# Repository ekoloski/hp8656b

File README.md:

## HP1820-3618 replacement

This project aims to use modern hardware to recreate the functionality of a mask rom microcontroller known as 1820-3618 in HP catalogs. It was used in the HP 8656B Signal Generator, and possibly other equipment, to interface the generators main cpu with both the fractional-n divider asic and various modulation circuits. It's a serial to parallel converter that also manages some gpio control lines.

The service manual describes a high level overview of the chips functions but lacks enough detail to create a suitable replacement. As I later found out, this firmware also does a couple of interesting things in response to a few serial commands I've never seen my 8656B issue. It also provides some routines for troubleshooting the rest of the circuitry.

### But...why go to the effort when you can just get one from a junk unit?

I purchased this signal generator on one of the auction sites with the understanding that it was for parts only and needed repair. My goal from the start was to restore the unit and use it as part of my electronics lab. After quite a bit of debugging I ultimately traced the issues to a failing adjustment potentiometer and a failed transistor. This is where the story should happily end, however it does not. In the course of troubleshooting I did some sloppy probing around A13U9 which led to the introduction of **-15V** to the 'Out of Lock' comparator output pin, which is directly connected to pin 11 of the 1820-3618, A13U28.

The chip never functioned properly after that event. The unit was not able to achieve PLL lock even after the original faults were discovered and repaired. I probed the serial input of A13U28 and found data. I then probed the 4 parallel output pins and the control lines, still no activity.

I was unable to find any information on this chip, labeled as a Motorola SC87336CP. Comparing the pinout in the 8656B service manual I found it to be fairly unique pinout in the world of Motorola 8bit microcontrollers of the time. Some educated guesses led me to the MC68705P5, which fit the description. I suspect that my chip is a mask rom variant of this microprocessor. Which is great, but without the ability to read the ROM I am still stuck.

Thinking that it was a lost cause to recreate the chip at this point I decided to purchase a second 8656B in much worse cosmetic condition. The part was harvested, transplanted, and the repaired unit works great. Everything should have been wonderful! Unfortunately I decided to investigate what in addition to a missing A13U28 was wrong with the donor unit. Much to my disappointment, the only problem was a faulty electrolytic capacitor. Of course I had to replace it but now I'm back to the start and stuck with an otherwise functional boat anchor in need of one unobtanium chip.

### Extracting the ROM

After quite a bit of reading I had come to the belief that the chip would need to be carefully decapped and photographed under a microscope. It could then be possible to locate the ROM on the die and optically recover the bits. I've seen it done on the internet, so it's got to be easy, right?

Probably not. So I shelved this project in lieu of some others and spent a while just not thinking about it. Then I did a little more research and came across the work by [Sean Riddle](http://seanriddle.com/mc68705p5.html). He details an obscure operating mode of the same family of CPU, and how he exploited it.

This mode is entered by powering the chip with /RESET /INT and TIMER high, and pulling PC0 high to 7.5V. When the micro comes out of reset it will ingest opcodes to execute from PortA. At the same time, an output is latched onto PortB. If the instruction on PortA happens to be 0x9d (nop) then the chip will simply continue to iterate through all 2K of it's address space. The output on PortB is a permutation of the current address, and the contents in memory. There is also apparently some data on PortC, but that's damaged on my chip so I didn't bother. I suspect it's the missing bits of the address.

As mentioned, the damage to my chip was conveniently located on PortC. Maybe there's hope that this method works on my particular mask rom, and that it's not too badly damaged? I figured it's worth a shot, so I breadboarded everything up and hooked up the scope.

To my amazement, there was data. A stream of it! The byte is sampled on the falling edge of each clock, 8 clocks are required to produce one byte of actual data, as it appears in the form of:
    {ADDR} {ADDR} {DATA} {DATA} {ADDR} {ADDR} {DATA} {DATA}

I noticed that the pattern was repeating at each 16K boundary, meaning we have a 2K address space. The chip will happily loop through and read out the address space until reset.

A healthy chunk of data was captured on the logic analyzer. The data was sifted from the noise to produce a raw dump.

### Interpreting the ROM

Next I needed to figure out what I was looking at. Nothing lined up with the memory mapping from the MC68705P5's datasheet. I realized that not only did the chip fetch an opcode from PortA, it fetched an address. The 0x9D must have been read in as $59D, meaning my capture started at 1437 bytes in! I shifted the data to realign it and it lined up perfectly with the memory map in the datasheet. I overwrote all non-ROM addresses with 0x9D to make disassembly easier and was ready to disassemble.

The [MAME project](https://www.mamedev.org/) has done a lot of work with this type of micro, and it's no surprise they have a nice disassembler called unidasm, which happily ingested the ROM from my crippled chip.

It took a moment and help from the Motorola M68HC05 Applications Guide, but I was able to wrap my head around the result. The only code I've written for microprocessors has been interrupt driven and was written in C. This is neither of those things. Instead it's beautify simple and elegant.

Beyond that, recreating the functionality of the chip be considerably more difficult without it. There are nuances that are not discussed in the service manual. I've also found that a test pin labeled as unused in the service manual does have a routine associated with it. Perhaps this chip was used in other equipment?

### Converting to something more modern

Now that I have the program from the chip and it's datasheet there's no reason not to create a modern replacement.

I decided on an Atmel ATMEGA32U4-MUR. It was available, came in a small enough package that I could build a board to fit the original DIP-28W, and had more than enough capability for the job. After creating a small breakout board and soldering pin headers to emulate the original DIP28W, I was ready to start adapting the program.

With how purpose built the code is, and with the role it plays in setting up things like the FM calibration and other support circuitry in the 8656B, I suspect that the timings involved may be somewhat critical. I likely wouldn't achieve anything as close to the original if I wrote it in C, unless I did a bunch of extra work. So, AVR8 it is.

### Again...why?

The chances of anyone else needing a replacement for an HP1820-3618 are pretty slim. The chances of finding this and needing a replacement? Negligible.

But I would bet that there are others who may find themselves, for whatever reason, wanting to get a peek into a similar mask rom. I'd be glad if it helps in that case and maybe even resurrects some piece of hardware. It's been a lot of fun, and I've rediscovered a bit of code that, in all likelihood, no one else has even looked at in at least the last 25 years.

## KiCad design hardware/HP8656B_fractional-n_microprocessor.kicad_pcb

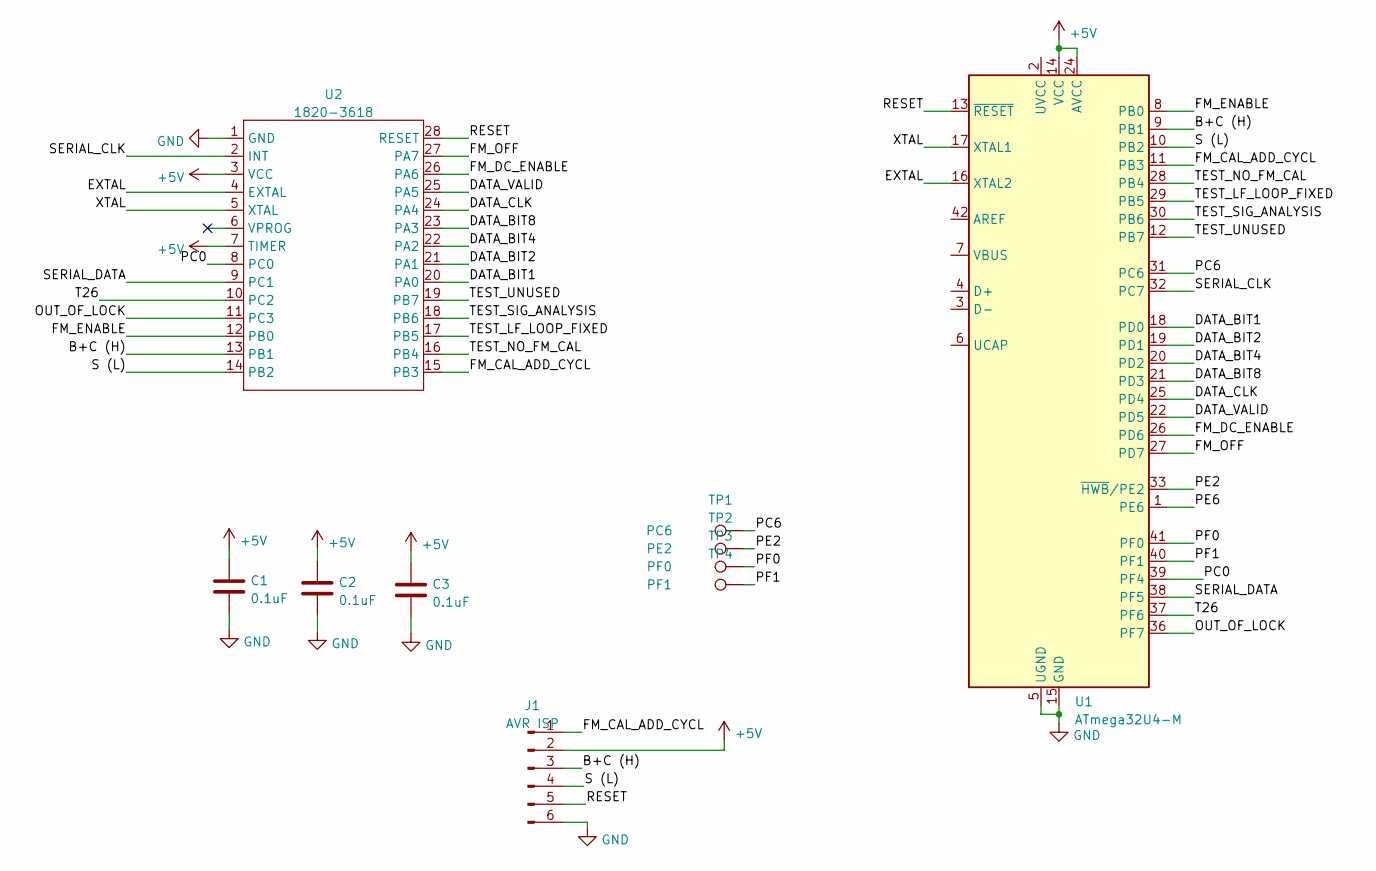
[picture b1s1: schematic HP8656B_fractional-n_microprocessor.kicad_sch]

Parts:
C1, C2, C3: 0.1uF; C_0603_1608Metric
J1: AVR ISP; PinHeader_2x03_P2.54mm_Vertical
TP1: PC6; TestPoint_Pad_D1.0mm
TP2: PE2; TestPoint_Pad_D1.0mm
TP3: PF0; TestPoint_Pad_D1.0mm
TP4: PF1; TestPoint_Pad_D1.0mm
U1: ATmega32U4-M; QFN-44-1EP_7x7mm_P0.5mm_EP5.2x5.2mm
U2: 1820-3618; DIP-28_W15.24mm_Socket

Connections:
+5V: C1.1, C2.1, C3.1, J1.2, U1.14 (VCC), U1.24 (AVCC), U1.34 (VCC), U1.44 (AVCC), U2.3 (VCC), U2.7 (TIMER)
/B+C (H): J1.3, U1.9 (PB1), U2.13 (PB1)
/DATA_BIT1: U1.18 (PD0), U2.20 (PA0)
/DATA_BIT2: U1.19 (PD1), U2.21 (PA1)
/DATA_BIT4: U1.20 (PD2), U2.22 (PA2)
/DATA_BIT8: U1.21 (PD3), U2.23 (PA3)
/DATA_CLK: U1.25 (PD4), U2.24 (PA4)
/DATA_VALID: U1.22 (PD5), U2.25 (PA5)
/EXTAL: U1.16 (XTAL2), U2.4 (EXTAL)
/FM_CAL_ADD_CYCL: J1.1, U1.11 (PB3), U2.15 (PB3)
/FM_DC_ENABLE: U1.26 (PD6), U2.26 (PA6)
/FM_ENABLE: U1.8 (PB0), U2.12 (PB0)
/FM_OFF: U1.27 (PD7), U2.27 (PA7)
/OUT_OF_LOCK: U1.36 (PF7), U2.11 (PC3)
/PC0: U1.39 (PF4), U2.8 (PC0)
/PC6: TP1.1, U1.31 (PC6)
/PE2: TP2.1, U1.33 (~HWB/PE2)
/PE6: U1.1 (PE6)
/PF0: TP3.1, U1.41 (PF0)
/PF1: TP4.1, U1.40 (PF1)
/RESET: J1.5, U1.13 (~RESET), U2.28 (RESET)
/S (L): J1.4, U1.10 (PB2), U2.14 (PB2)
/SERIAL_CLK: U1.32 (PC7), U2.2 (INT)
/SERIAL_DATA: U1.38 (PF5), U2.9 (PC1)
/T26: U1.37 (PF6), U2.10 (PC2)
/TEST_LF_LOOP_FIXED: U1.29 (PB5), U2.17 (PB5)
/TEST_NO_FM_CAL: U1.28 (PB4), U2.16 (PB4)
/TEST_SIG_ANALYSIS: U1.30 (PB6), U2.18 (PB6)
/TEST_UNUSED: U1.12 (PB7), U2.19 (PB7)
/XTAL: U1.17 (XTAL1), U2.5 (XTAL)
GND: C1.2, C2.2, C3.2, J1.6, U1.5 (UGND), U1.15 (GND), U1.23 (GND), U1.35 (GND), U1.43 (GND), U1.45 (GND), U2.1 (GND)

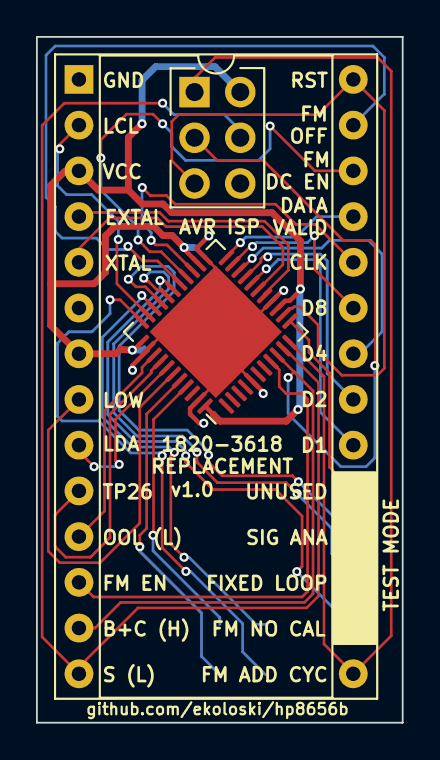
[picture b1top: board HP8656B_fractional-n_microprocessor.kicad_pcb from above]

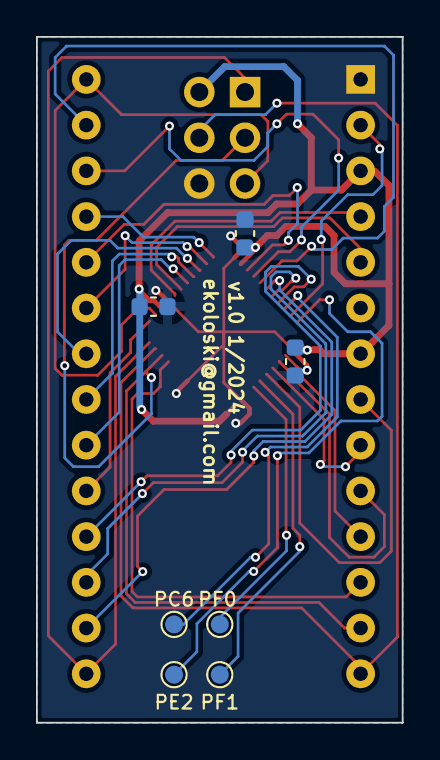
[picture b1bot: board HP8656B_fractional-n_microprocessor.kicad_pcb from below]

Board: 2 copper layers, 20.3 x 38.1 mm, 10 parts (7 on the bottom side), 30 nets.

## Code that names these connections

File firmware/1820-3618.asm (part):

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    out     SPH,r16             ;

    ldi     r16,0xFF            ;
    out     DDRD,r16            ; set PORTD PD0:7 Output
    ldi     r16,0x05            ;
    out     PORTB,r16           ; set PB0 `fm_en` and PB2`S_L` high
    ldi     r16,0x0F            ;
    out     DDRB,r16            ; set PB0:PB3 Output
    ldi     r16,0xF0            ; 
    out     PORTB,r16           ; Set pull-ups on test mode input pins PB4:7
    sbi     PORTC,7             ; set PC7 pull-up
    sbi     PORTC,6             ; set PC6 pull-up `TP26`

    sbis    PINF,6
    rjmp    test_mode_tp26      ; if PF6 `TP26` is low then jump to TP26 routine
    rjmp    main                ; otherwise proceed to main program

test_mode_tp26:
    sbis    PINB,5                          ; if PB5 `Test mode fixed loop` is LOW
    jmp     testmode_lf_loop_vco_fixed      ;  jump to fixed loop routine
    sbis    PINB,6                          ; if PB6 `Signal Analysis` mode is LOW 
    jmp     testmode_signature_analysis     ;  jump to sig ana routine
    sbis    PINB,7
    jmp     testmode_unused                 ; if PB7 `Unused` is LOW jump to unused test routine
                                            ; Service manual lists as unused, but it jumps into
                                            ; signal analysis at an alternate point.
    rjmp    test_mode_tp26                  ; We're stuck here until a test mode is selected
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    ld      r16,X               ; Load the first word from the buffer and wait to receive
receive_command:
    sbic    PINC,7
    rjmp    receive_command     ; wait for PC7 `SCL` to go low
    sbis    PINF,5              ; 
    clc                         ; funny little dance
    sbic    PINF,5              ; to get the data bit into the carry bit
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                                ;  It's cooler in m6805 due to the indexed address mode on rol    
command_clockwait:
    sbis    PINC,7
    rjmp    command_clockwait   ; wait for PC7 `SCL` to go high
    brcc    receive_command     ; Loop to receive the word
    st      X,r16
    sbrs    r16,3               ; check if command is 0-7 and go run it
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    ld      r16,x
receive_bits:
    sbic    PINC,7
    rjmp    receive_bits        ; wait for PC7 `SCL` to go low
    sbis    PINF,5
    clc                         ; Transfer to carry
    sbic    PINF,5
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command_1:                      ; Report the status of OOL on the Serial Data line
    cbi     PORTF,5             ; This is used in the built-in self tests under option `6`
    sbic    PINF,7              ;
    sbi     PORTF,5             ; Transfer status of PF7 `OOL` to PF5 `SDA`
    ldi     r16,0x20            ;
    out     DDRF,r16            ; set PF5 `serial data in` as output
    ldi     r16,0x0D            ; Delay a moment
command_1_delay:
    dec     r16
    brne    command_1_delay
    ldi     r16,0x00
    out     DDRF,r16            ; Set PF5 `serial data in` back to an input
    sbi     PORTF,5             ; Set the pullup on PF5
    jmp     main                ; Back to program start

command_2:                      ; FM Disable
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    ret

                                ; 4-bit parallel data out. Data is valid on rising edge of clk
                                ; This also preserves the status of control lines PD6:7
tx_parallel_data:               ; Wake up the Fractional-N controller
    ldi     r16,0x01            ; Set r16 to 0x01
    ld      r17,Y               ; Load the status byte into r17
    or      r16,r17
    out     PORTD,r16           ; Set PD0 `D1` high
    ori     r16,0x20
    out     PORTD,r16           ; Set PD5 `data_valid`
    nop                         ; Pulse stretcher
    andi    r16,0xCF            ; Clear data_valid and clk bits
    out     PORTD,r16
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    ldi     XH,HIGH(sStatus)
    ld      r16,X
    ori     r16,0x40
    out     PORTD,r16           ; Set PD6 `fm_dc_en` set the remaining bits from sStatus
    ldi     r16,0x0B
    out     PORTB,r16           ; Set `fm_en`, `B+C` and `fm_add_cyc`
    call    delay_60mS          ; wait 60 milliseconds
    sbi     PORTB,2             ; Set PB2 `S (L)` pin
    cbi     PORTB,3             ; Clear PB3 `fm_add_cyc` pin
fm_cal_delay:
    ldi     r16,0x08            ; 
    out     OCR0A,r16           ; Set compareA to 0x08, about 5mS
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    inc     r16
    cpi     r16,0x2e            ;
    brne    fm_cal_delay_2
    cbi     PORTB,1             ; Clear PB1 `B+C H`
    eor     r16,r16             ; Clock/Prescaler comination don't have enough resolution
fm_cal_delay_3:                 ; Extra delay before setting port back to stored status
    inc     r16
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    ld      r16,X               ; Load sStatus into r16
    sbrc    r16,7               ; Keep 'fm_en' pin set if status was already enabled
    rjmp    fm_cal_done
    cbi     PORTB,0             ; Otherwise clear PB0 `fm_en` pin
fm_cal_done:
    ldi     XL,LOW(sStatus)
    ldi     XH,HIGH(sStatus)
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                                        ; low, the signature at the related pin is the alternate
                                        ; signature

                                        ;PB0 TP24 CLK fm_enable
                                        ;PB1 TP25 DSA B+C L (start_stop)
                                        ;OOL is LOW when LED is lit

                                        ;PIN            NORMAL      ALTERNATE   Condition
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                                        ;6(VPP)         0000        ----        ----
                                        ;7(HIGH)        7U39        ----        ----
                                        ;8(LOW)         0000        ----        ----
                                        ;9(SDA)         0000        7U39        PF5 pulled high
                                        ;10(TP26)       7U39        0000        PF6 tied low
                                        ;11(OOL)        7U39        0000        Out of Lock LED on
                                        ;14(S (L))      0021        0020        INT pin low
                                        ;15(fm_add_cyc  0010        40C5        RAM Error
                                        ;16(S (L))      7U39        0000        PB4 tied low
                                        ;17(fixed_loop) 7U39        0000        PB5 tied low
                                        ;18(sig_ana)    7U39        0000        PB6 tied low
                                        ;19(unused)     7U39        0000        PB7 tied low
                                        ;20(D1)         2050        2052        PF4 low
                                        ;21(D2)         102C        1029        PF5 low
                                        ;22(D4)         0816        0814        PF6 low
                                        ;23(D8)         0408        040A        Out of Lock LED ON
                                        ;24(PCLK)       0201        0205        PB4 low
                                        ;25(data_valid) 0105        0102        PB5 low
                                        ;26(fm_dc_en)   0085        0081        PB6 low
                                        ;27(fm_off)     0044        0040        PB7 low
                                        ;28 RESET       7U39        ----        ----
testmode_signature_analysis:
    ldi     r16,0x00
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    brcc    ramtest_resetX      ; branch if carry is clear to start over
    rjmp    rampass
ramfail:
    sbi     PORTB,3             ; Set PB3 `fm_add_cyc`
rampass:
    eor     r17,r17             ; Clock/Prescaler combination doesn't have enough resolution.
ramtest_padding:                ; Timing here is not critical, regardless a delay is added
    inc     r17                 ; to more closely match the original.
    cpi     r17,0x02
    brne    ramtest_padding
    sbi     PORTB,1             ; Set bit PB1 `B+C H` (Open SA window)
    call    dsa_clock           ; Clock the signature analyzer
    cbi     PORTB,3             ; Clear bit PB3 `fm_add_cyc`
    ldi     r16,0x01
bit_shift_loop:                 ; Walk a bit through PORTD
    out     PORTD,r16           ; Update PORTD
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    brcc    bit_shift_loop      ; Walk through the entire port
    clr     r16
    out     PORTD,r16           ; Clear PORTD
    sbi     PORTB,2             ; Set PB2 `S (L)`
    call    dsa_clock           ;
    cbi     PORTB,2             ; Clear PB2 `S (L)`
    sbi     PORTB,3             ; Set PB3 `FM_CAL_ADD_CYC`
    call    dsa_clock           ;
    cbi     PORTB,3             ; Clear PB3 `FM_CAL_ADD_CYC`
    clr     r16
    out     PORTD,r16           ; Clear PORTD
    call    dsa_clock           ; Clock the signature analyzer
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    out     PORTD,r16           ; Clear PORTD
    jmp     testmode_unused

dsa_clock:                      ; Deliver a brief pulse to `fm_en` pin PB0
    sbi     PORTB,0
    nop
    nop
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    ret

testmode_unused:
    sbis    PINC,7              ; If PC7 `serial_clock_in` is low then clear PB2 and clock sig ana
    rjmp    test_mode_1
    sbi     PORTB,2             ; Otherwise set PB2 `S (L)`
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
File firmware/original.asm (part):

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00000080: a6 ff     lda   #$FF          ;
00000082: b7 04     sta   $04           ;set PORTA output
00000084: a6 80     lda   #$80          ;
00000086: b7 00     sta   $00           ;set PA7 (fm_off) high
00000088: b7 40     sta   $40           ;
0000008a: a6 0f     lda   #$0F          ;
0000008c: b7 05     sta   $05           ;set PB0:PB3 output
0000008e: a6 05     lda   #$05          ;
00000090: b7 01     sta   $01           ;set PB0 and PB2 `fm_en` and `S (L)` high
00000092: a6 00     lda   #$00
00000094: b7 06     sta   $06           ;set PORTC input

                                        ; Check test mode `TP26` is low
00000096: 05 02 03  brclr 2, $02, $09C  ;if PC2 `TP26` is low branch and check which mode to run
00000099: cc 03 c0  jmp   $03C0         ;else jump to the main program

0000009c: 0a 01 03  brset 5, $01, $0A2  ;if PB5 `TEST MODE FIXED LOOP` is low
0000009f: cc 05 b3  jmp   $05B3         ;jump to $5B3 [Test Mode Fixed Loop]

000000a2: 0c 01 03  brset 6, $01, $0A8  ;if PB6 (TEST MODE SIG ANA) is low
000000a5: cc 05 f0  jmp   $05F0         ;jump to $5F0 [Test Mode SIG ANA]

000000a8: 0e 01 f1  brset 7, $01, $09C  ;if PB7 (TEST MODE UNUSED) is low
000000ab: cc 06 64  jmp   $0664         ;jump to $664 [Test Mode UNUSED]
          ; Service manual lists this as unused but it jumps into an alternate point of sig analysis

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00000420: a4 02     anda  #$02          ;
00000422: b7 02     sta   $02           ;
00000424: a6 02     lda   #$02          ;
00000426: b7 06     sta   $06           ;Set PC1 as an output (Serial Data Pin)
00000428: ae 0d     ldx   #$0D          ;
0000042a: 5a        decx                ;
0000042b: 26 fd     bne   $42A          ; delay loop (52 cycles about 13 uS)
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                                        ; [Send all 16 words and associated control signals]
0000046b: a6 01     lda   #$01          ; load 0x01 into A
0000046d: ba 40     ora   $40           ; or sStatus with A
0000046f: b7 00     sta   $00           ;store A into PortA setting PA0 `D1` and PA6 `fm_dc_en`
00000471: aa 20     ora   #$20          ;or A with 0x20 (0x61)
00000473: b7 00     sta   $00           ;bring PA5 `data_valid` high as well
00000475: a4 cf     anda  #$CF          ;
00000477: b7 00     sta   $00           ;clear PA5 `data_valid`
00000479: ae 06     ldx   #$06          ;
0000047b: 5a        decx                ;
0000047c: 26 fd     bne   $47B          ; delay
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00000564: a6 0b     lda   #$0B          ;
00000566: b7 01     sta   $01           ;set `fm_en`, `B+C`, and `fm_add_cyc`
00000568: cd 05 98  jsr   $0598         ;delay
0000056b: 14 01     bset  2, $01        ;set PB2 `S (L)`
0000056d: 17 01     bclr  3, $01        ;clear PB3 `FM Add Cycle`
0000056f: a6 27     lda   #$27          ;
00000571: b7 08     sta   $08           ;
00000573: 3f 09     clr   $09           ;
00000575: 0f 09 fd  brclr 7, $09, $575  ;Calibrated delay
00000578: 13 01     bclr  1, $01        ;clear PB1 `B+C`
0000057a: ae 05     ldx   #$05          ;
0000057c: 5a        decx                ;
0000057d: 26 fd     bne   $57C          ;delay
0000057f: 0e 40 02  brset 7, $40, $584  ;skip if bit 7 of $40 is set
00000582: 11 01     bclr  0, $01        ;clear bit PB0 `FM EN`
00000584: b6 40     lda   $40           ;
00000586: b7 00     sta   $00           ;
00000588: 05 02 01  brclr 2, $02, $58C  ;skip extra delay if `TP26` is low
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                                        ;   A3TP17 to GND
                                        ; The alternate signature at pins 14, 20, 27 check the input at pins 2, 8 to 11 and 16 to 19. When the input is low, the signature at the related pin is the alternate signature

                                        ;PB0 TP24 CLK fm_enable
                                        ;PB1 TP25 DSA B+C L

                                        ;PIN            NORMAL      ALTERNATE   Condition
                                        ;1(VSS)         0000        ----        ---
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                                        ;6(VPP)         0000        ----        ----
                                        ;7(HIGH)        7U39        ----        ----
                                        ;8(LOW)         0000        ----        ----
                                        ;9(SDA)         0000        7U39        PC1 pulled high
                                        ;10(TP26)       7U39        0000        PC2 tied low
                                        ;11(OOL)        7U39        0000        Out of Lock LED on
                                        ;14(S (L))      0021        0020        INT pin low
                                        ;15(fm_add_cyc  0010        40C5        RAM Error
                                        ;16(S (L))      7U39        0000        PB4 tied low
                                        ;17(fixed_loop) 7U39        0000        PB5 tied low
                                        ;18(sig_ana)    7U39        0000        PB6 tied low
                                        ;19(unused)     7U39        0000        PB7 tied low
                                        ;20(D1)         2050        2052        PC0 low
                                        ;21(D2)         102C        1029        PC1 low
                                        ;22(D4)         0816        0814        PC2 low
                                        ;23(D8)         0408        040A        Out of Lock LED ON
                                        ;24(PCLK)       0201        0205        PB4 low
                                        ;25(data_valid) 0105        0102        PB5 low
                                        ;26(fm_dc_en)   0085        0081        PB6 low
                                        ;27(fm_off)     0044        0040        PB7 low
                                        ;28 RESET       7U39        ----        ----
                                        ;
000005f0: 3f 00     clr   $00           ;clear portA
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00000601: ab 11     adda  #$11          ;otherwise add 0x11 to A
00000603: 24 f1     bcc   $5F6          ; jump to back to the start if carry is clear
00000605: 20 02     bra   $609          ;do NOT set fm_add_cyc bit
00000607: 16 01     bset  3, $01        ;set PB3 `fm_add_cyc`
00000609: 12 01     bset  1, $01        ;set PB1 `b+c H`

0000060b: cd 06 5f  jsr   $065F         ;DSA Clock (pulse `fm_en`)
0000060e: 17 01     bclr  3, $01        ;clear PB3 `fm_add_cyc`

00000610: a6 01     lda   #$01          ;
bit_shift_loop:
00000612: b7 00     sta   $00           ;store A into PortA
00000614: cd 06 5f  jsr   $065F         ;DSA Clock (pulse `fm_en`)
00000617: 48        asla                ;left shift A
00000618: 24 f8     bcc   $612          ; jump back to set PA0 if carry is clear
0000061a: 3f 00     clr   $00           ;clear PortA
0000061c: 14 01     bset  2, $01        ;set PORTB bit 2 `S (L)`
0000061e: cd 06 5f  jsr   $065F         ;DSA Clock (pulse `fm_en`)
00000621: 15 01     bclr  2, $01        ;clear PORTB bit 2 `S (L)`
00000623: 16 01     bset  3, $01        ;set PORTB bit 3 `FM_CAL_ADD_CYC`
00000625: cd 06 5f  jsr   $065F         ;DSA Clock (pulse `fm_en`)
00000628: 17 01     bclr  3, $01        ;clear PB3 `fm_add_cyc`

0000062a: 3f 00     clr   $00           ;clear PortA
0000062c: cd 06 5f  jsr   $065F         ;DSA Clock (pulse `fm_en`)
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
00000638: b6 02     lda   $02           ;load portC into A
0000063a: a4 0f     anda  #$0F          ;blank out the top 4 bits of PortC that always read high
0000063c: b7 00     sta   $00           ;Mirror PC0:3's contents to PA0:3

0000063e: cd 06 5f  jsr   $065F         ;DSA Clock (pulse `fm_en`)
00000641: 3f 00     clr   $00           ;clear PortA

                                        ; [Test Mode: UNUSED]
00000643: 2e 04     bil   $649          ;jump to $649 if interrupt line is low (Serial Clock)
00000645: 14 01     bset  2, $01        ;set PB2 `S (L)`
00000647: 20 02     bra   $64B          ;jump to $64B
00000649: 15 01     bclr  2, $01        ;clear PB2 `S (L)`
0000064b: cd 06 5f  jsr   $065F         ;DSA Clock (pulse `fm_en`)
0000064e: 13 01     bclr  1, $01        ;clear PB1 `B+C (H)`
00000650: cd 06 5f  jsr   $065F         ;DSA Clock (pulse `fm_en`)

00000653: a6 28     lda   #$28          ;
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
                                        ; [dsa_clock]
                                        ;Used in signal analysis and unused test modes
0000065f: 10 01     bset  0, $01        ;set PB0 `fm_en`
00000661: 11 01     bclr  0, $01        ;clear PB0`fm_en`
00000663: 81        rts                 ;return from subroutine

00000664: 20 fe     bra   $664          ;halt

          *SELF-TEST ROM
          *putting 9V on TIMER input shifts vectors up 8 bytes
          *for self-test, loop high bits (7-4) to low bits (3-0) of ports A and B, connect PA7 to \INT
          *results are output on port C - data sheet just says that LEDs should flash, no specific error codes
          *self-test reset jumps here

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
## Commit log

2024-02-21 Minor updates and fixes

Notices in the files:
firmware/1820-3618.asm:
Copyright 2024 Edward Koloski <ekoloski@gmail.com>
Licensed under MIT (https://github.com/ekoloski/hp8656b/LICENSE)
